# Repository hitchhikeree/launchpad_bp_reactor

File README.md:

Reactor LaunchPad BoosterPack
=========================

3-axis accelerometer, gyroscope, and magnetometer sensors coupled with an IR proximity sensor and RGB color sensor. Useful for robotics, flying drones, and the like.

## Project Links
- <a href="http://www.hitchhikeree.org/reactor/">HitchhikerEE page</a>
- <a href="http://youtu.be/DQJmf79zrzc">YouTube video</a>
- <a href="https://docs.google.com/folder/d/0B5HjtPsFD8u5YVA3ZUJud2s5a2c/edit?usp=sharing">Design files on Google Drive</a>
- <a href="http://e2e.ti.com/group/microcontrollerprojects/m/boosterpackcontest/664830.aspx">LaunchPad BoosterPack Contest page</a>

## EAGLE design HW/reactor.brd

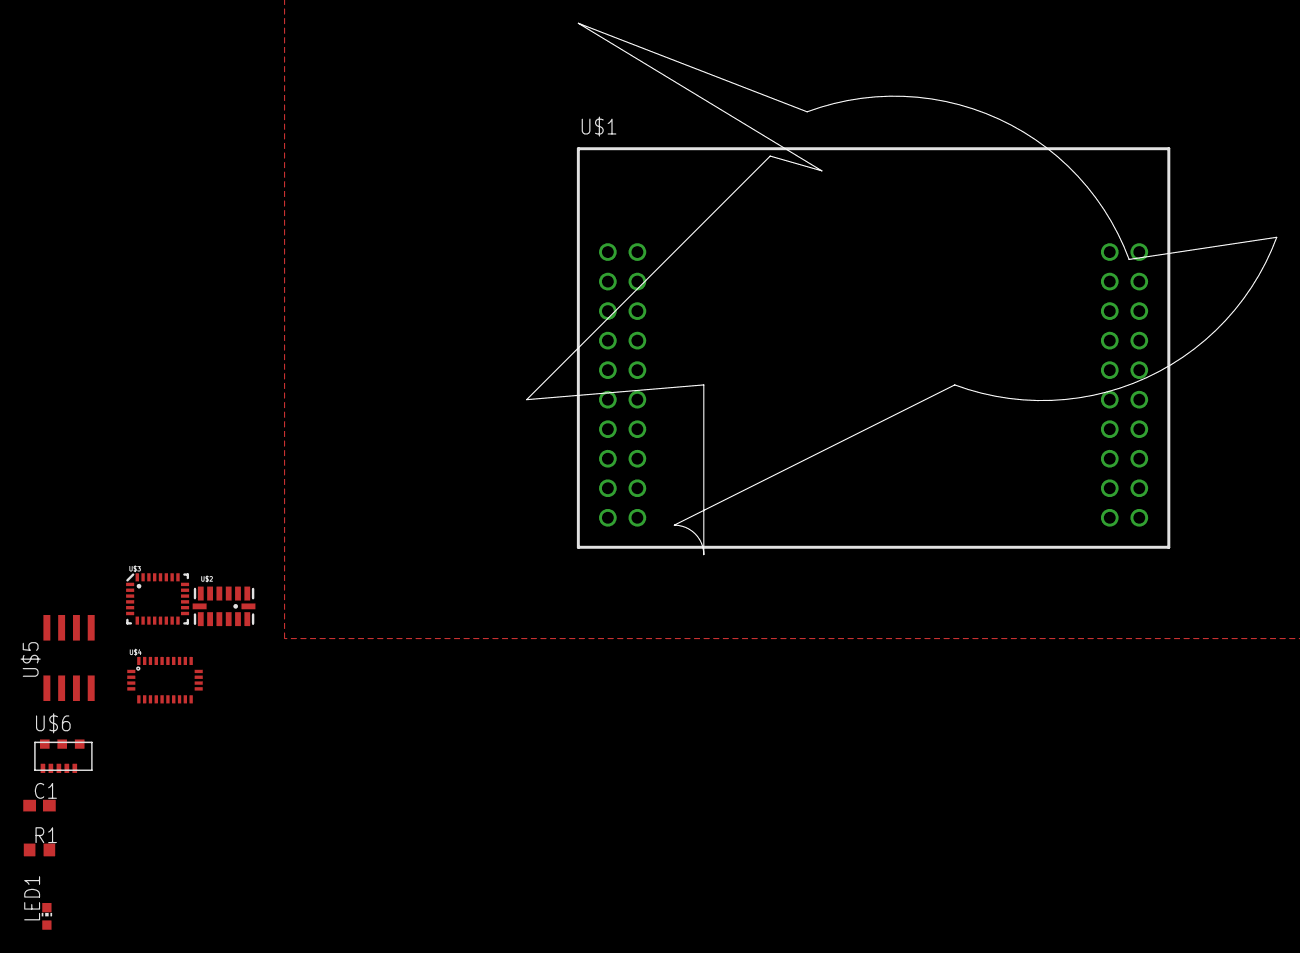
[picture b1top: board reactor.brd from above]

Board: 2 copper layers, 64.5 x 45.7 mm, 9 parts (0 on the bottom side), 2 nets, no tracks yet.

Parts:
C1: C0603
LED1: CHIP-LED0603
R1: R0603
U$1: LAUNCHPAD_BOOSTER_PACK
U$2: LGA14
U$3: LGA28-4X5
U$4: LGA28
U$5: SOIC8
U$6: VCNL3020

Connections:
GND: U$1.GND@1, U$1.GND@2, U$5.4, U$6.VSS
VDD: U$5.5, U$6.VDD

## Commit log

2013-02-24 Adding base CAD files
2013-03-02 Finished design
